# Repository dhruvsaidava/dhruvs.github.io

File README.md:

# dhruvsaidava.github.io
Dhruv Saidava | Portfolio

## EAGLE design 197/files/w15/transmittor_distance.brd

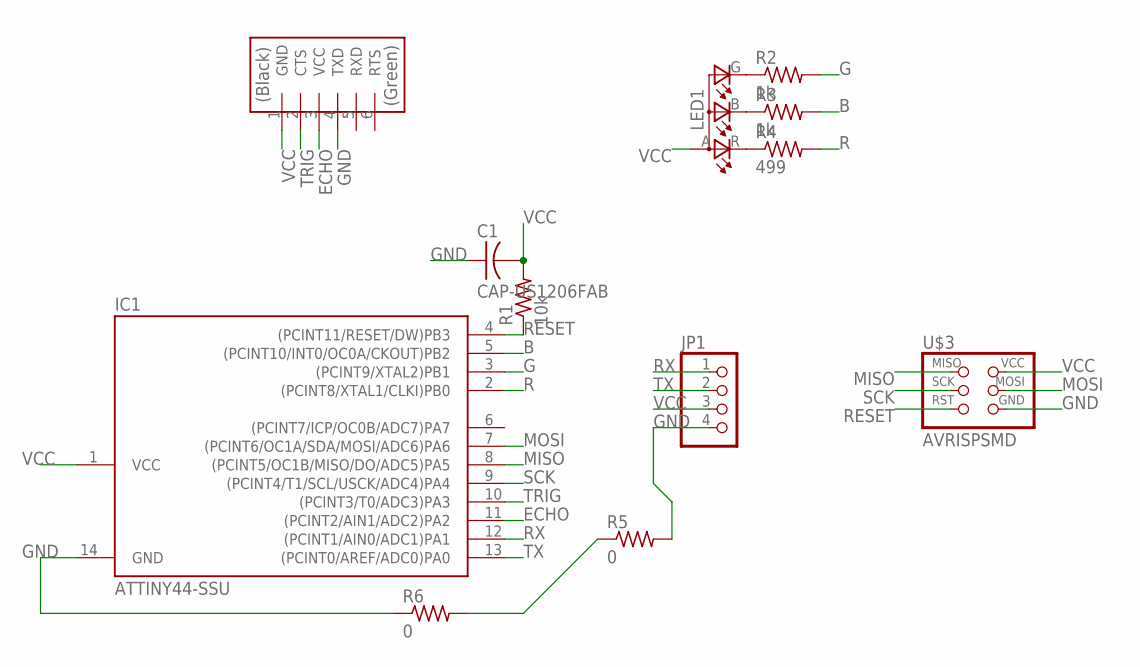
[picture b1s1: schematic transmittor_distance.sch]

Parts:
C1: CAP-US1206FAB; C1206FAB
IC1: ATTINY44-SSU; SOIC14
JP1: PINHD-1X4; 1X04
LED1: LEDRGBOLD; P-LCC-4-3
R1: 10k; R1206FAB
R2, R3: 1k; R1206FAB
R4: 499; R1206FAB
R5, R6: 0; R1206FAB
U$1: FTDI-SMD-HEADER; 1X06SMD
U$3: AVRISPSMD; 2X03SMD

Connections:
B: IC1.5 ((PCINT10/INT0/OC0A/CKOUT)PB2), R3.2
ECHO: IC1.11 ((PCINT2/AIN1/ADC2)PA2), U$1.3 (VCC)
G: IC1.3 ((PCINT9/XTAL2)PB1), R2.2
GND: C1.1, IC1.14 (GND), JP1.4, R5.2, R6.1, U$1.4 (TXD), U$3.6 (GND)
MISO: IC1.8 ((PCINT5/OC1B/MISO/DO/ADC5)PA5), U$3.1 (MISO)
MOSI: IC1.7 ((PCINT6/OC1A/SDA/MOSI/ADC6)PA6), U$3.4 (MOSI)
unnamed: R5.1, R6.2
unnamed: LED1.G (CGREEN), R2.1
unnamed: LED1.B (CBLUE), R3.1
unnamed: LED1.R (CRED), R4.1
R: IC1.2 ((PCINT8/XTAL1/CLKI)PB0), R4.2
RESET: IC1.4 ((PCINT11/RESET/DW)PB3), R1.1, U$3.5 (RST)
RX: IC1.12 ((PCINT1/AIN0/ADC1)PA1), JP1.1
SCK: IC1.9 ((PCINT4/T1/SCL/USCK/ADC4)PA4), U$3.3 (SCK)
TRIG: IC1.10 ((PCINT3/T0/ADC3)PA3), U$1.2 (CTS)
TX: IC1.13 ((PCINT0/AREF/ADC0)PA0), JP1.2
VCC: C1.2, IC1.1 (VCC), JP1.3, LED1.A (A2), R1.2, U$1.1 (GND), U$3.2 (VCC)

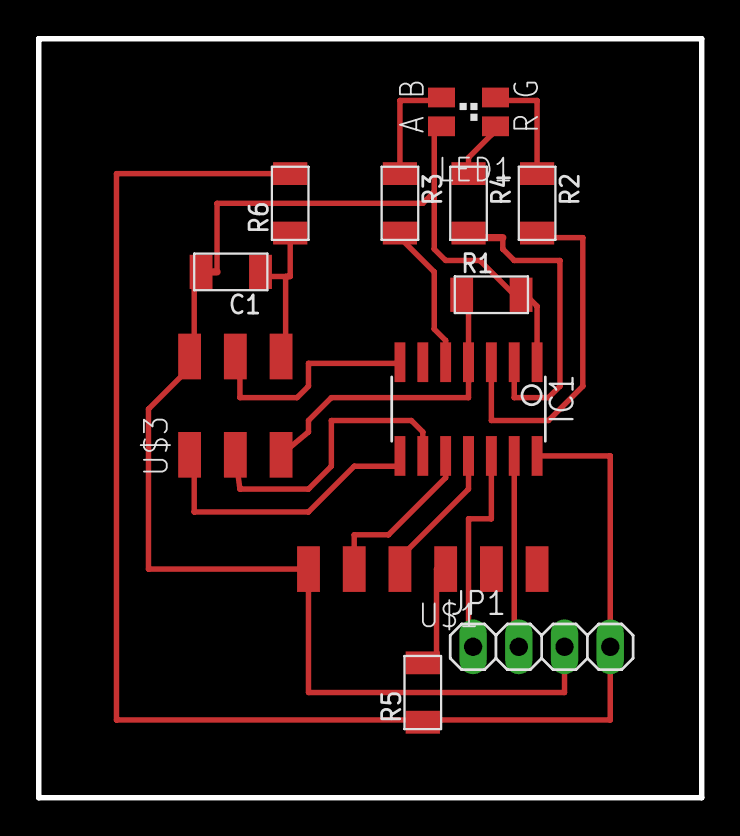
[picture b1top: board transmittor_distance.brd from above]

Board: 2 copper layers, 36.8 x 42.2 mm, 12 parts (0 on the bottom side), 17 nets.

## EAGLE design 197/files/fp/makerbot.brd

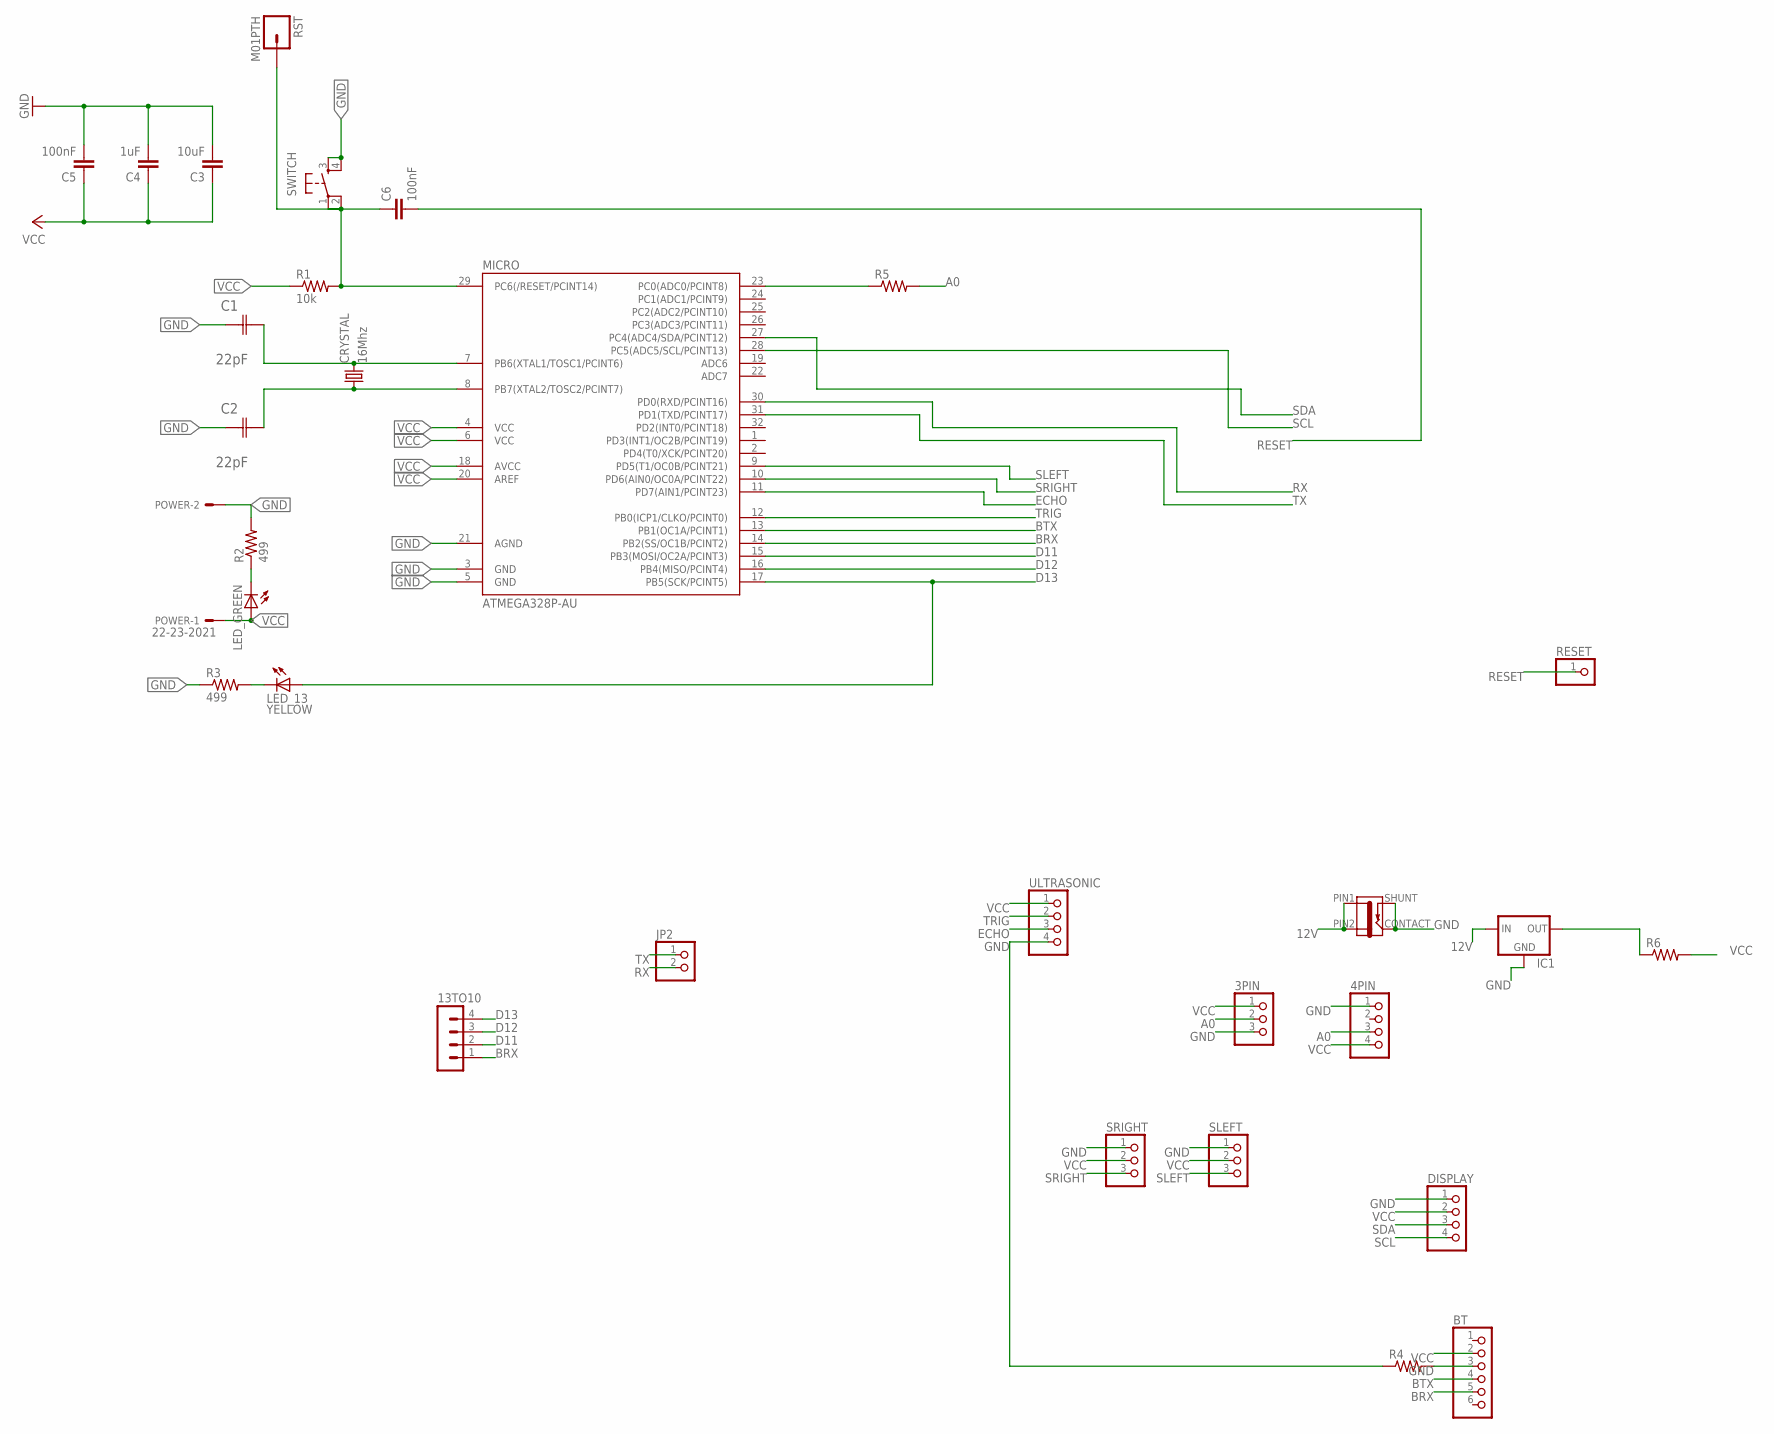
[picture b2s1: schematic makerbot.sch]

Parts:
3PIN: PINHD-1X3; 1X03
4PIN: PINHD-1X4; 1X04
13TO10: MA04-1
BT: PINHD-1X6; 1X06
C1, C2: 22pF; CAPC3216X178N
C3: 10uF; 1206
C4: 1uF; 1206
C5, C6: 100nF; 1206
CRYSTAL: 16Mhz; CSM-7X-DU
DISPLAY: PINHD-1X4; 1X04
IC1: 78XXL
J1: JACK-2.1MM; PJ-002AH-SMT
JP2: PINHD-1X2; 1X02
LED_13: YELLOW; 1206
LED_GREEN: LED1206; 1206
MICRO: ATMEGA328P-AU; TQFP32-08
POWER: 22-23-2021
R1: 10k; 1206
R2, R3: 499; 1206
R4, R5, R6: RES-US1206FAB; R1206FAB
RESET: PINHD-1X1; 1X01
RST: M01PTH; 1X01
SLEFT: PINHD-1X3; 1X03
SRIGHT: PINHD-1X3; 1X03
SWITCH: 6MM_SWITCH6MM_SWITCH; 6MM_SWITCH
ULTRASONIC: PINHD-1X4; 1X04

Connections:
12V: IC1.IN, J1.PIN1, J1.PIN2
A0: 3PIN.2, 4PIN.3, MICRO.23 (PC0(ADC0/PCINT8)), R5.1, R5.2
BRX: 13TO10.1, BT.5, MICRO.14 (PB2(SS/OC1B/PCINT2))
BTX: BT.4, MICRO.13 (PB1(OC1A/PCINT1))
D11: 13TO10.2, MICRO.15 (PB3(MOSI/OC2A/PCINT3))
D12: 13TO10.3, MICRO.16 (PB4(MISO/PCINT4))
D13: 13TO10.4, LED_13.1 (A), MICRO.17 (PB5(SCK/PCINT5))
ECHO: MICRO.11 (PD7(AIN1/PCINT23)), ULTRASONIC.3
GND: 3PIN.3, 4PIN.1, BT.3, C1.1 (C1), C2.1 (C1), C3.2, C4.2, C5.2, DISPLAY.1, IC1.GND, J1.CONTACT, J1.SHUNT, MICRO.3 (GND), MICRO.5 (GND), MICRO.21 (AGND), POWER.2, R2.2, R3.1, R4.1, R4.2, SLEFT.1, SRIGHT.1, SWITCH.3 (S), SWITCH.4 (S1), ULTRASONIC.4
unnamed: C1.2 (C2), CRYSTAL.2, MICRO.7 (PB6(XTAL1/TOSC1/PCINT6))
unnamed: C2.2 (C2), CRYSTAL.1, MICRO.8 (PB7(XTAL2/TOSC2/PCINT7))
unnamed: LED_GREEN.2 (C), R2.1
unnamed: LED_13.2 (C), R3.2
unnamed: C6.1, MICRO.29 (PC6(/RESET/PCINT14)), R1.2, RST.1, SWITCH.1, SWITCH.2 (P1)
RESET: C6.2, RESET.1
RX: JP2.2, MICRO.30 (PD0(RXD/PCINT16))
SCL: DISPLAY.4, MICRO.28 (PC5(ADC5/SCL/PCINT13))
SDA: DISPLAY.3, MICRO.27 (PC4(ADC4/SDA/PCINT12))
SLEFT: MICRO.9 (PD5(T1/OC0B/PCINT21)), SLEFT.3
SRIGHT: MICRO.10 (PD6(AIN0/OC0A/PCINT22)), SRIGHT.3
TRIG: MICRO.12 (PB0(ICP1/CLKO/PCINT0)), ULTRASONIC.2
TX: JP2.1, MICRO.31 (PD1(TXD/PCINT17))
VCC: 3PIN.1, 4PIN.4, BT.2, C3.1, C4.1, C5.1, DISPLAY.2, IC1.OUT, LED_GREEN.1 (A), MICRO.4 (VCC), MICRO.6 (VCC), MICRO.18 (AVCC), MICRO.20 (AREF), POWER.1, R1.1, R6.1, R6.2, SLEFT.2, SRIGHT.2, ULTRASONIC.1

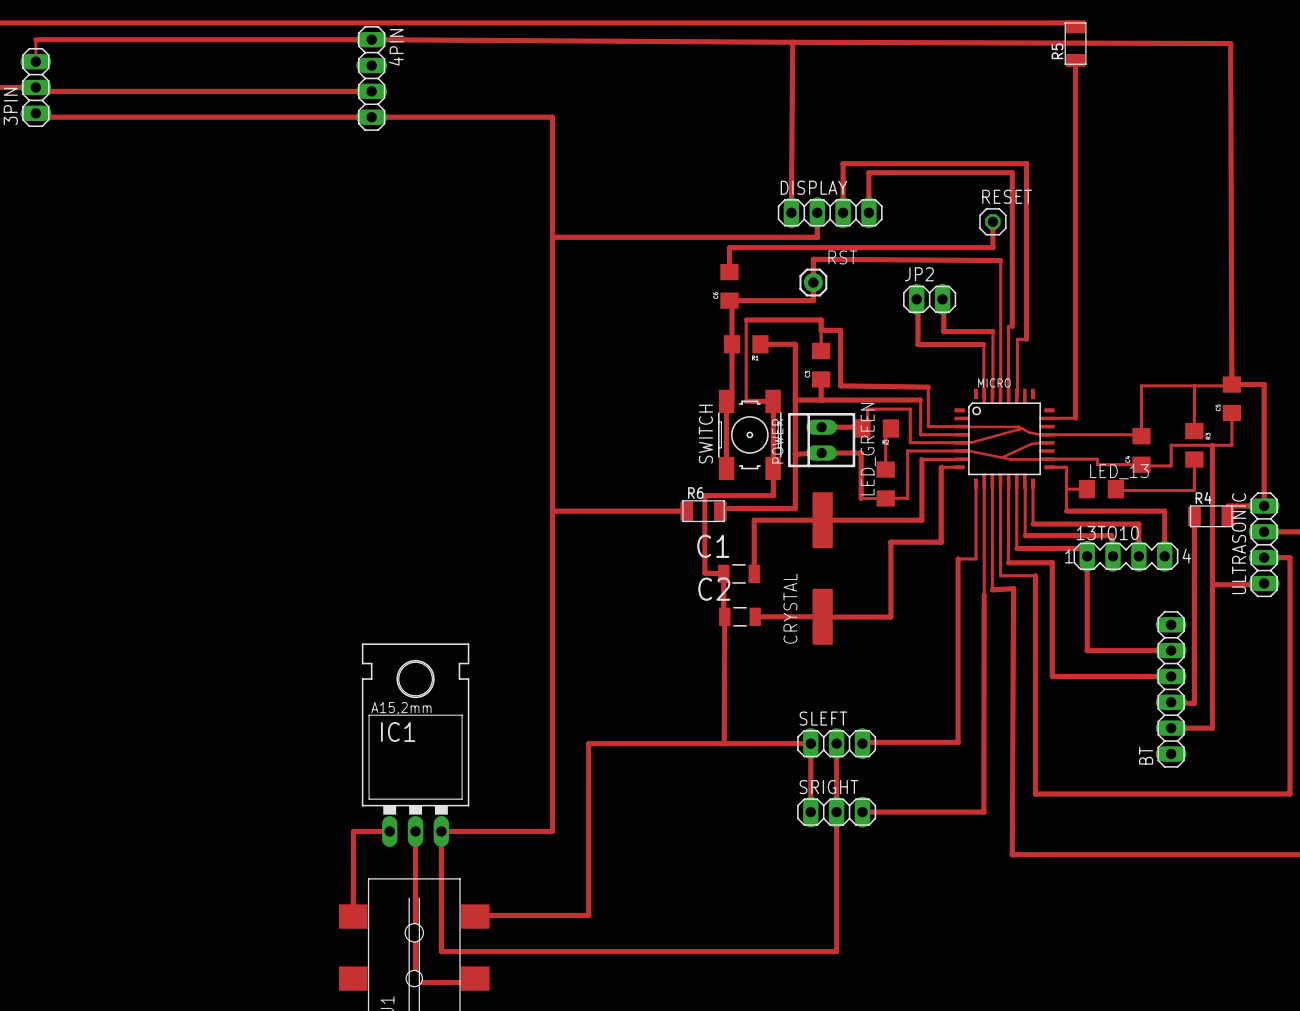
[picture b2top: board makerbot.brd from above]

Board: 2 copper layers, 31 parts (0 on the bottom side), 23 nets.

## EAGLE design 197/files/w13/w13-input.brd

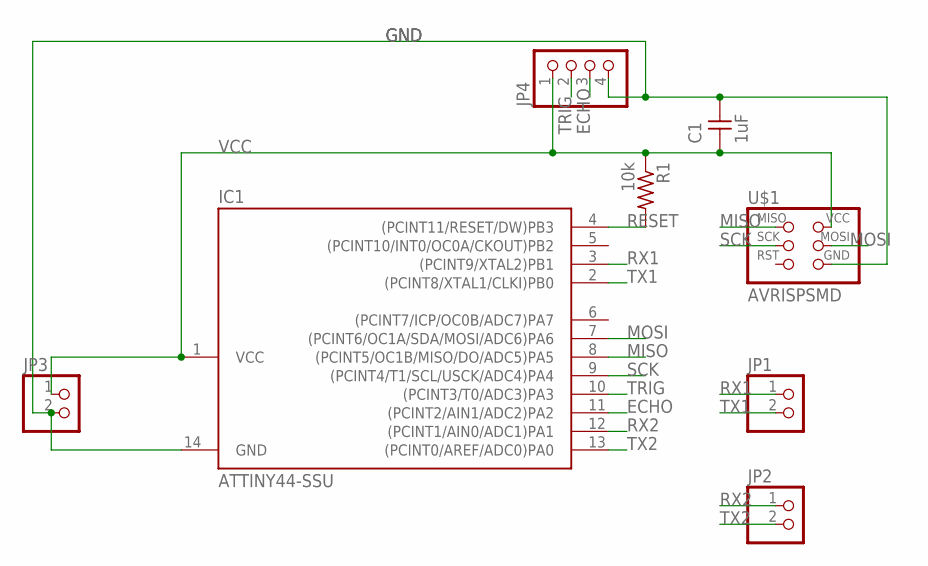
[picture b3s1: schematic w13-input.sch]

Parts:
C1: 1uF; C1206FAB
IC1: ATTINY44-SSU; SOIC14
JP1, JP2, JP3: PINHD-1X2; 1X02
JP4: PINHD-1X4; 1X04
R1: 10k; R1206FAB
U$1: AVRISPSMD; 2X03SMD

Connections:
ECHO: IC1.11 ((PCINT2/AIN1/ADC2)PA2), JP4.3
GND: C1.2, IC1.14 (GND), JP3.2, JP4.4, U$1.6 (GND)
MISO: IC1.8 ((PCINT5/OC1B/MISO/DO/ADC5)PA5), U$1.1 (MISO)
MOSI: IC1.7 ((PCINT6/OC1A/SDA/MOSI/ADC6)PA6), U$1.4 (MOSI)
RESET: IC1.4 ((PCINT11/RESET/DW)PB3), R1.2
RX1: IC1.3 ((PCINT9/XTAL2)PB1), JP1.1
RX2: IC1.12 ((PCINT1/AIN0/ADC1)PA1), JP2.1
SCK: IC1.9 ((PCINT4/T1/SCL/USCK/ADC4)PA4), U$1.3 (SCK)
TRIG: IC1.10 ((PCINT3/T0/ADC3)PA3), JP4.2
TX1: IC1.2 ((PCINT8/XTAL1/CLKI)PB0), JP1.2
TX2: IC1.13 ((PCINT0/AREF/ADC0)PA0), JP2.2
VCC: C1.1, IC1.1 (VCC), JP3.1, JP4.1, R1.1, U$1.2 (VCC)

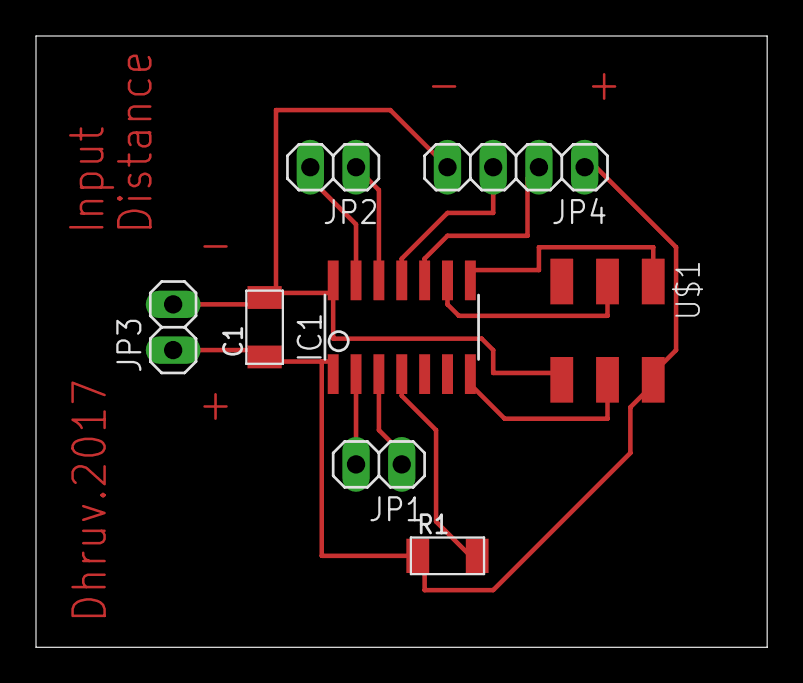
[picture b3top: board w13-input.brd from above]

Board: 2 copper layers, 40.6 x 34.0 mm, 8 parts (0 on the bottom side), 12 nets.

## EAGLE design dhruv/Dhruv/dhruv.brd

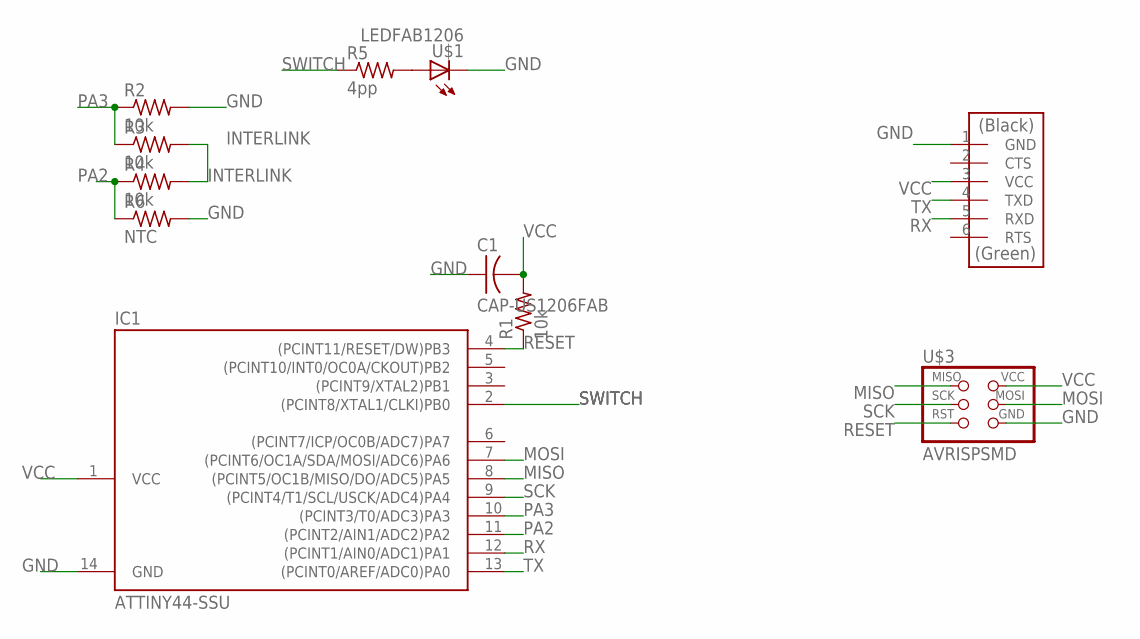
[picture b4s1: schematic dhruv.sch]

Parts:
C1: CAP-US1206FAB; C1206FAB
IC1: ATTINY44-SSU; SOIC14
R1, R2, R3, R4: 10k; R1206FAB
R5: 4pp; R1206FAB
R6: NTC; R1206FAB
U$1: LEDFAB1206; LED1206FAB
U$2: FTDI-SMD-HEADER; 1X06SMD
U$3: AVRISPSMD; 2X03SMD

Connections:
GND: C1.1, IC1.14 (GND), R2.2, R6.2, U$1.2 (C), U$2.1 (GND), U$3.6 (GND)
INTERLINK: R3.2, R4.2
MISO: IC1.8 ((PCINT5/OC1B/MISO/DO/ADC5)PA5), U$3.1 (MISO)
MOSI: IC1.7 ((PCINT6/OC1A/SDA/MOSI/ADC6)PA6), U$3.4 (MOSI)
unnamed: R5.2, U$1.1 (A)
PA2: IC1.11 ((PCINT2/AIN1/ADC2)PA2), R4.1, R6.1
PA3: IC1.10 ((PCINT3/T0/ADC3)PA3), R2.1, R3.1
RESET: IC1.4 ((PCINT11/RESET/DW)PB3), R1.1, U$3.5 (RST)
RX: IC1.12 ((PCINT1/AIN0/ADC1)PA1), U$2.5 (RXD)
SCK: IC1.9 ((PCINT4/T1/SCL/USCK/ADC4)PA4), U$3.3 (SCK)
SWITCH: IC1.2 ((PCINT8/XTAL1/CLKI)PB0), R5.1
TX: IC1.13 ((PCINT0/AREF/ADC0)PA0), U$2.4 (TXD)
VCC: C1.2, IC1.1 (VCC), R1.2, U$2.3 (VCC), U$3.2 (VCC)

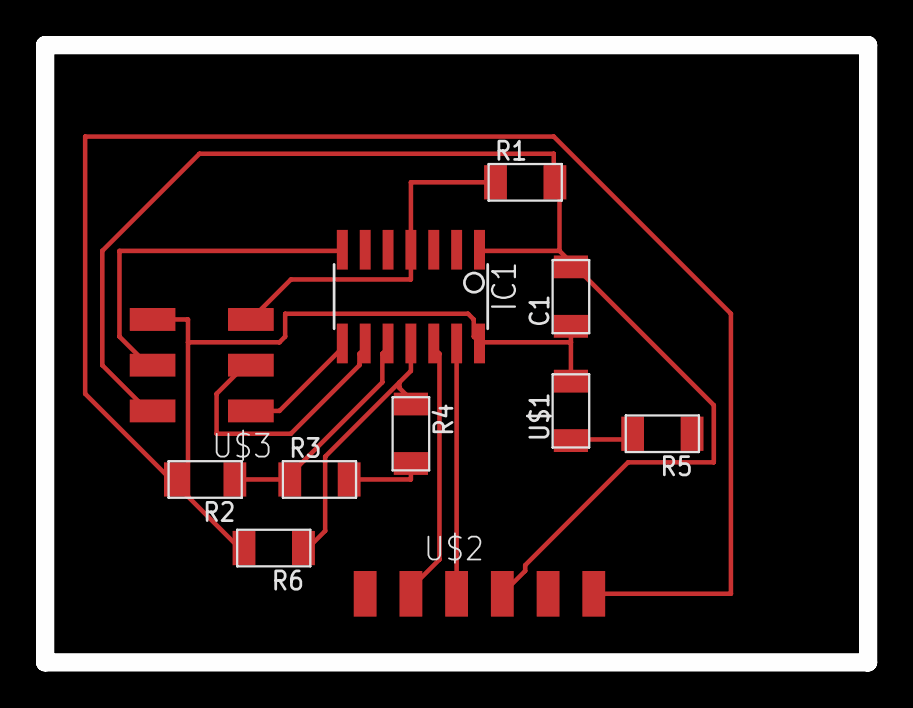
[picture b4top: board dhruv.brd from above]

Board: 2 copper layers, 45.7 x 34.3 mm, 11 parts (0 on the bottom side), 13 nets.

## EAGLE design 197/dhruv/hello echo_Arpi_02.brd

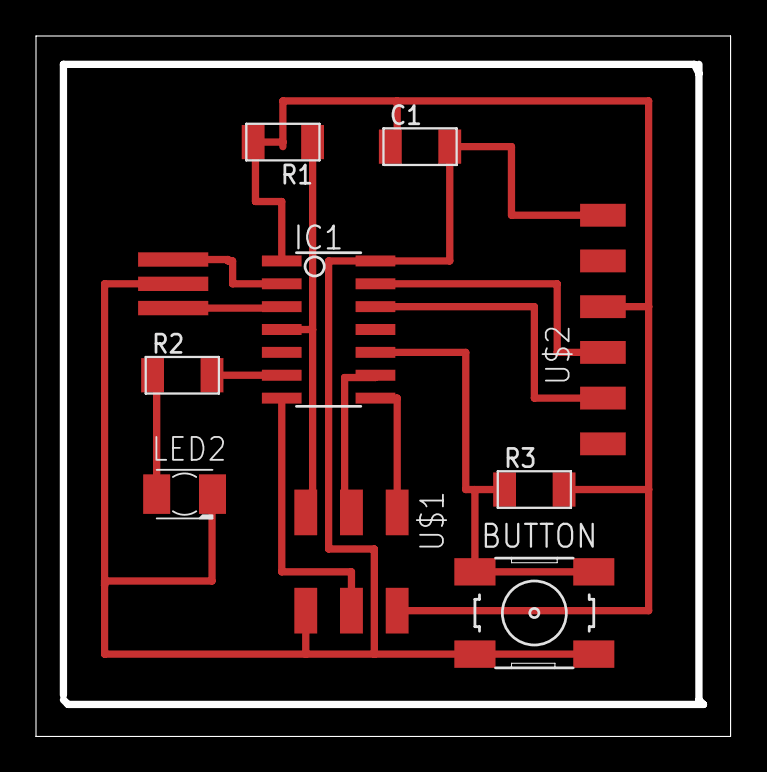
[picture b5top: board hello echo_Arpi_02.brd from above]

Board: 2 copper layers, 38.6 x 38.9 mm, 10 parts (0 on the bottom side), 13 nets.

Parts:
BUTTON: 0; 6MM_SWITCH
C1: CAP-US1206FAB; C1206FAB
IC1: ATTINY44-SSU; SOIC14
LED2: KA-3528ASYC
R1: 10k; R1206FAB
R2: 499; R1206FAB
R3: 10K; R1206FAB
U$1: AVRISPSMD; 2X03SMD
U$2: FTDI-SMD-HEADER; 1X06SMD
U$3: RESONATOR; EFOBM

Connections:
BUTTON: BUTTON.1, BUTTON.2, IC1.10, R3.1
GND: BUTTON.3, BUTTON.4, C1.2, IC1.14, LED2.C, U$1.6, U$2.1, U$3.2
LED: IC1.6, R2.2
MISO: IC1.8, U$1.1
MOSI: IC1.7, U$1.4
unnamed: LED2.A, R2.1
unnamed: IC1.2, U$3.1
unnamed: IC1.3, U$3.3
RST: IC1.4, R1.1, U$1.5
RX: IC1.12, U$2.5
SCK: IC1.9, U$1.3
TX: IC1.13, U$2.4
VCC: C1.1, IC1.1, R1.2, R3.2, U$1.2, U$2.3

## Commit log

2017-02-10 New Web
2017-02-10 Index Ch
2017-03-01 Create CNAME
2017-06-25 Added CV
2017-06-29 Cname Addded
2017-09-09 composites edited
2017-10-03 HTMl added
2017-10-03 Carasoul
2017-10-03 Images added
2017-10-03 About content added
2017-10-03 3 content added o about us:
2017-10-05 3d scanning edited
2017-10-06 Footer editied
2017-10-08 Pure CSS
2017-10-09 SID added
2017-10-10 slider added
2017-10-23 composites
2017-10-23 cemter done
2017-10-24 Molding Process updated
2017-10-24 Casting process added Image left
2017-10-24 Flies added w12
2017-10-24 Heading Changed
2017-10-24 Formating
2017-10-24 Molding photos added
2017-10-24 Formatting
2017-10-24 Composite Done
2017-10-24 Composite completed
2017-10-25 CNC updated
2017-10-25 CNC Completed
2017-10-25 Machine Design Week
2017-10-26 Licence Work Completed
2017-10-28 All updated
2017-10-28 screen shot added
2017-10-29 week 1 tutorials added
2017-10-29 Week 2 Tutorials & References added
2017-10-29 Updated Formatting, Computer controlled cutting
2017-10-29 All Weeks Tutorials & References added
2017-10-29 Project Develoment
2017-10-29 footer margin-top added
2017-10-29 style.css added
2017-10-29 style.css update
2017-10-29 image resize
2017-10-29 Removed Unwanted Images
2017-10-29 Beautification done
2017-10-29 style changes
2017-10-29 structure update
2017-10-29 week 10 added
2017-10-30 Output week update
2017-10-30 spell update
2017-10-30 p3d.in iframe
2017-10-30 container container-main update
2017-10-30 footer update
2017-10-30 File Added
2017-10-30 satshakit info added
2017-10-30 Molding casting formating
2017-10-30 Adding output files
2017-10-30 fab isp components
2017-10-30 formatted html week 4
2017-10-30 panel updateweek 4
2017-10-30 references update week 4
2017-10-30 Images location changed
2017-10-30 op devices image update
2017-10-30 justification
2017-10-30 final sketch added to index page
2017-10-30 week 2
2017-10-30 siti 3d
2017-10-30 rcm file added
2017-10-30 ap & imp
2017-10-31 input week component added
2017-10-31 Completed till week 3
2017-10-31 w10-milling
2017-10-31 Files Added to w10
2017-10-31 input week images added
2017-10-31 electronics design
2017-10-31 files added in every page
2017-10-31 rearrange
2017-10-31 merged final project & project dev.
2017-10-31 image added fp
2017-10-31 week 3
2017-10-31 license stuff
2017-10-31 links update w1
2017-10-31 molding week completed
2017-10-31 videos
2017-10-31 net & comm
2017-10-31 fp edit
2017-10-31 interface
2018-01-18 git template
2018-04-09 CSS added
2018-04-09 Css changed
2018-04-09 Css changedin 1 week
2018-05-11 webmaster verification
2018-05-26 RP Website updated
2018-05-26 Index upadted with title images
2018-05-27 week 9 rp added
2018-05-30 week 12, 13, 19 updated
2018-05-30 week 12, 13, 19 updated with video
2018-05-30 week 9 updated with video
2018-06-02 Molding and Casting
2018-10-21 Update CNAME

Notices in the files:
parts and their libraries:
01_SparkFun: Licensing: CC v3.0 Share-Alike You are welcome to use this library for commercial purposes.
